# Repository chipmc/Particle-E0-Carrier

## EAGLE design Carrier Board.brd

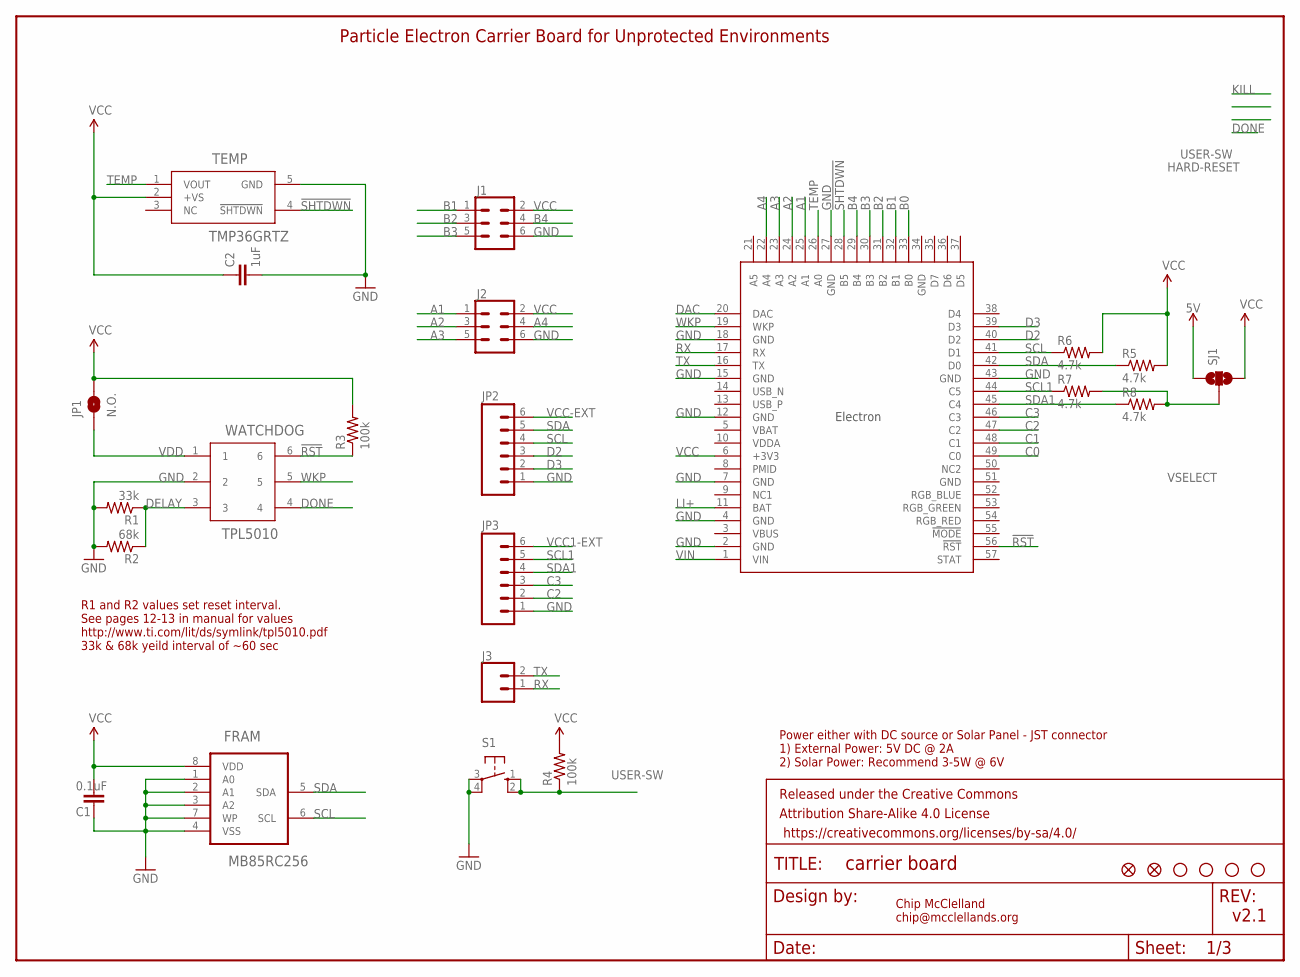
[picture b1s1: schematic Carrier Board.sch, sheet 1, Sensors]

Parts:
C1: 0.1uF; 0805
C2: 1uF; 0805
FD1, FD2: FIDUCIALUFIDUCIAL; FIDUCIAL-MICRO
FRAM: MB85RC256; SOIC127P600X175-8N
FRAME1: FRAME-LETTER; CREATIVE_COMMONS
J1, J2: CONN_03X22X3_SILK_MALE_PTH; 2X3
J3: CONN_02; 1X02
JP1: N.O.; SMT-JUMPER_2_NO_SILK
JP2, JP3: M06LOCK; 1X06_LOCK
JP4, JP5, JP6, JP7: STAND-OFF
R1: 33k; 0805
R2: 68k; 0805
R3, R4: 100k; 0805
R5, R6, R7, R8: 4.7k; 0805
S1: 10-XX; B3F-10XX
SJ1: SOLDERJUMPER_2WAYPASTE1&2; SJ_3_PASTE1&2
TEMP: TMP36GRTZ; RJ_5
U$1: E0-NOT-OFFICIAL
WATCHDOG: TPL5010; TSOT-23

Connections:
5V: SJ1.1; also elsewhere on the board
!RST: R3.1, U$1.56 (!RST), WATCHDOG.6
!SHTDWN: TEMP.4 (!SHTDWN), U$1.28 (B5)
A1: J2.1, U$1.25 (A1)
A2: J2.3, U$1.24 (A2)
A3: J2.5, U$1.23 (A3)
A4: J2.4, U$1.22 (A4)
B0: U$1.33 (B0)
B1: J1.1, U$1.32 (B1)
B2: J1.3, U$1.31 (B2)
B3: J1.5, U$1.30 (B3)
B4: J1.4, U$1.29 (B4)
C0: U$1.49 (C0)
C1: U$1.48 (C1)
C2: JP3.2, U$1.47 (C2); also elsewhere on the board
C3: JP3.3, U$1.46 (C3); also elsewhere on the board
D2: JP2.3, U$1.40 (D2); also elsewhere on the board
D3: JP2.2, U$1.39 (D3); also elsewhere on the board
DAC: U$1.20 (DAC)
DELAY: R1.1, R2.1, WATCHDOG.3
DONE: WATCHDOG.4
GND: C1.2, C2.2, FRAM.1 (A0), FRAM.2 (A1), FRAM.3 (A2), FRAM.4 (VSS), FRAM.7 (WP), J1.6, J2.6, JP2.1, JP3.1, R1.2, R2.2, S1.3, S1.4 (P1), TEMP.5 (GND), U$1.7 (GND), U$1.18 (GND), U$1.27 (GND), U$1.43 (GND), WATCHDOG.2; also elsewhere on the board
LI+: U$1.11 (BAT); also elsewhere on the board
RX: J3.1, U$1.17 (RX)
SCL: FRAM.6 (SCL), JP2.4, R6.1, U$1.41 (D1); also elsewhere on the board
SCL1: JP3.5, R7.1, U$1.44 (C5); also elsewhere on the board
SDA: FRAM.5 (SDA), JP2.5, R5.1, U$1.42 (D0); also elsewhere on the board
SDA1: JP3.4, R8.1, U$1.45 (C4); also elsewhere on the board
TEMP: TEMP.1 (VOUT), U$1.26 (A0)
TX: J3.2, U$1.16 (TX)
USER-SW: R4.1, S1.1 (S), S1.2 (S1)
VCC: C1.1, C2.1, FRAM.8 (VDD), J1.2, J2.2, JP1.2, R3.2, R4.2, R5.2, R6.2, SJ1.3, TEMP.2 (+VS), U$1.6 (+3V3); also elsewhere on the board
VCC1-EXT: JP3.6; also elsewhere on the board
VCC-EXT: JP2.6; also elsewhere on the board
VDD: JP1.1, WATCHDOG.1
VIN: U$1.1 (VIN); also elsewhere on the board
VSELECT: R7.2, R8.2, SJ1.2; also elsewhere on the board
WKP: U$1.19 (WKP), WATCHDOG.5

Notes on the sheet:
Chip McClelland chip@mcclellands.org
v2.1
Power either with DC source or Solar Panel - JST connector 1) External Power: 5V DC @ 2A 2) Solar Power: Recommend 3-5W @ 6V
Particle Electron Carrier Board for Unprotected Environments
R1 and R2 values set reset interval. See pages 12-13 in manual for values http://www.ti.com/lit/ds/symlink/tpl5010.pdf 33k & 68k yeild interval of ~60 sec

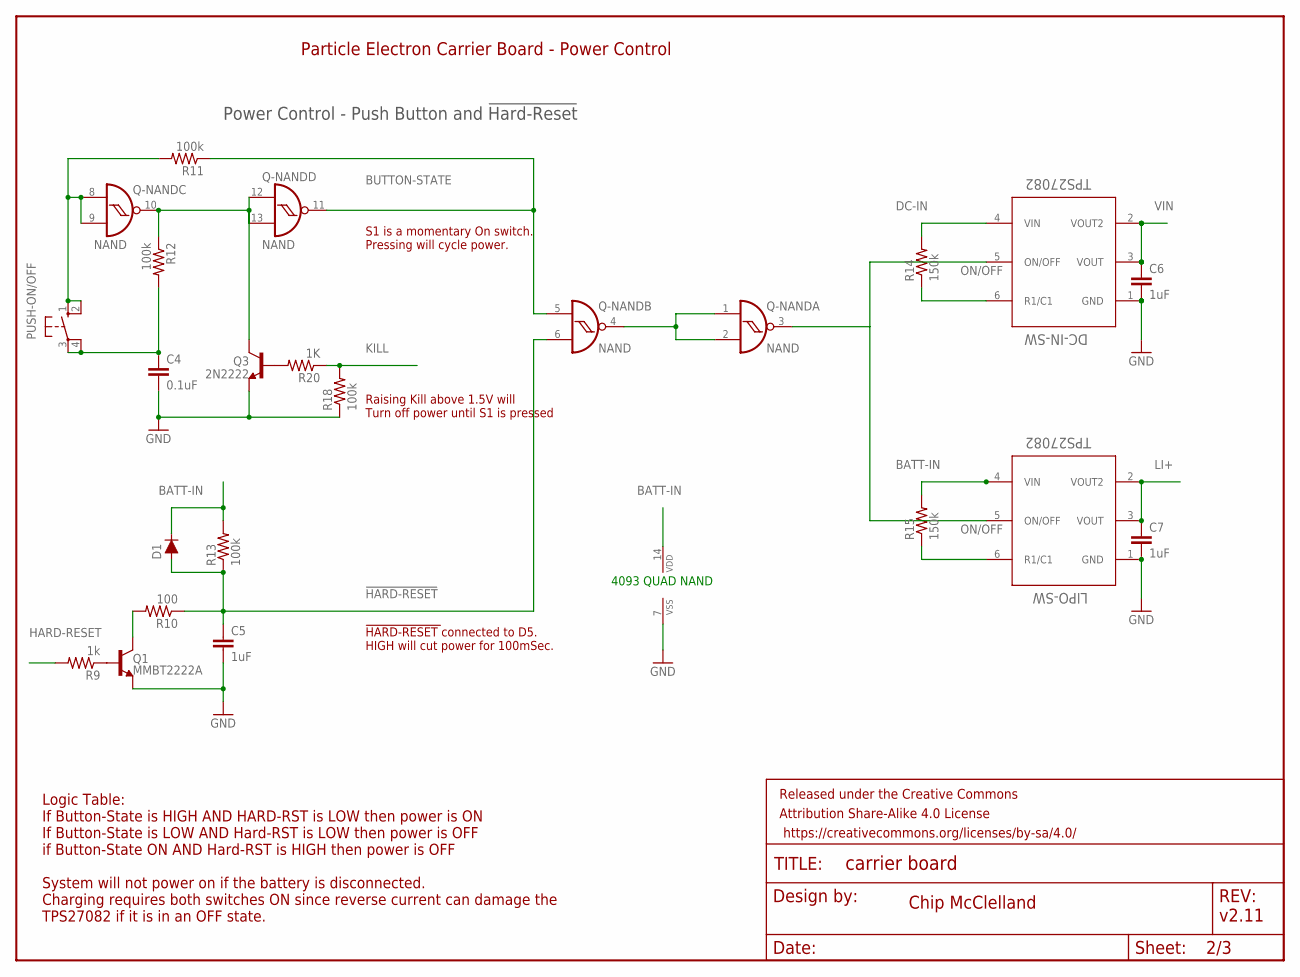
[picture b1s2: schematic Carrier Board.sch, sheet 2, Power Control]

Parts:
C4: 0.1uF; 0805
C5, C6, C7: 1uF; 0805
D1: DIODE-BAS16J; SOD-323
DC-IN-SW: TPS27082; TSOT-23
FRAME2: FRAME-LETTER; CREATIVE_COMMONS
LIPO-SW: TPS27082; TSOT-23
PUSH-ON/OFF: 40-XX-ROUND; B3F-40XX-ROUND
Q1: MMBT2222A; SOT23-3
Q3: 2N2222; SOT23-BEC
Q-NAND: NAND; MC14093B-TSSOP14
R9: 1k; 0805
R10: 100; 0805
R11, R12, R13, R18: 100k; 0805
R14, R15: 150k; 0805
R20: 1K; R0805

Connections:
!HARD-RESET: C5.1, D1.A, Q-NAND.6 (I1), R10.1, R13.1
BATT-IN: D1.C, LIPO-SW.4 (VIN), Q-NAND.14 (VDD), R13.2, R15.2; also elsewhere on the board
BUTTON-STATE: Q-NAND.5 (I0), Q-NAND.11 (O), R11.1
DC-IN: DC-IN-SW.4 (VIN), R14.2; also elsewhere on the board
GND: C4.2, C5.2, C6.2, C7.2, DC-IN-SW.1 (GND), LIPO-SW.1 (GND), Q1.2 (E), Q3.E, Q-NAND.7 (VSS), R18.1; also elsewhere on the board
HARD-RESET: R9.2
KILL: R18.2, R20.1
LI+: C7.1, LIPO-SW.2 (VOUT2), LIPO-SW.3 (VOUT); also elsewhere on the board
unnamed: Q-NAND.1 (I0), Q-NAND.2 (I1), Q-NAND.4 (O)
unnamed: Q3.B, R20.2
unnamed: Q3.C, Q-NAND.10 (O), Q-NAND.12 (I0), Q-NAND.13 (I1), R12.1
unnamed: DC-IN-SW.6 (R1/C1), R14.1
unnamed: Q1.1 (B), R9.1
unnamed: LIPO-SW.6 (R1/C1), R15.1
unnamed: Q1.3 (C), R10.2
unnamed: C4.1, PUSH-ON/OFF.3, PUSH-ON/OFF.4 (P1), R12.2
unnamed: PUSH-ON/OFF.1 (S), PUSH-ON/OFF.2 (S1), Q-NAND.8 (I0), Q-NAND.9 (I1), R11.2
ON/OFF: DC-IN-SW.5 (ON/OFF), LIPO-SW.5 (ON/OFF), Q-NAND.3 (O)
VIN: C6.1, DC-IN-SW.2 (VOUT2), DC-IN-SW.3 (VOUT); also elsewhere on the board

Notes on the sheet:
Particle Electron Carrier Board - Power Control
4093 QUAD NAND
Power Control - Push Button and !Hard-Reset
Chip McClelland
v2.11
Logic Table: If Button-State is HIGH AND HARD-RST is LOW then power is ON If Button-State is LOW AND Hard-RST is LOW then power is OFF if Button-State ON AND Hard-RST is HIGH then power is OFF System will not power on if the battery is disconnected. Charging requires both switches ON since reverse 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
!HARD-RESET !connected to D5. HIGH will cut power for 100mSec.
S1 is a momentary On switch. Pressing will cycle power.
Raising Kill above 1.5V will Turn off power until S1 is pressed

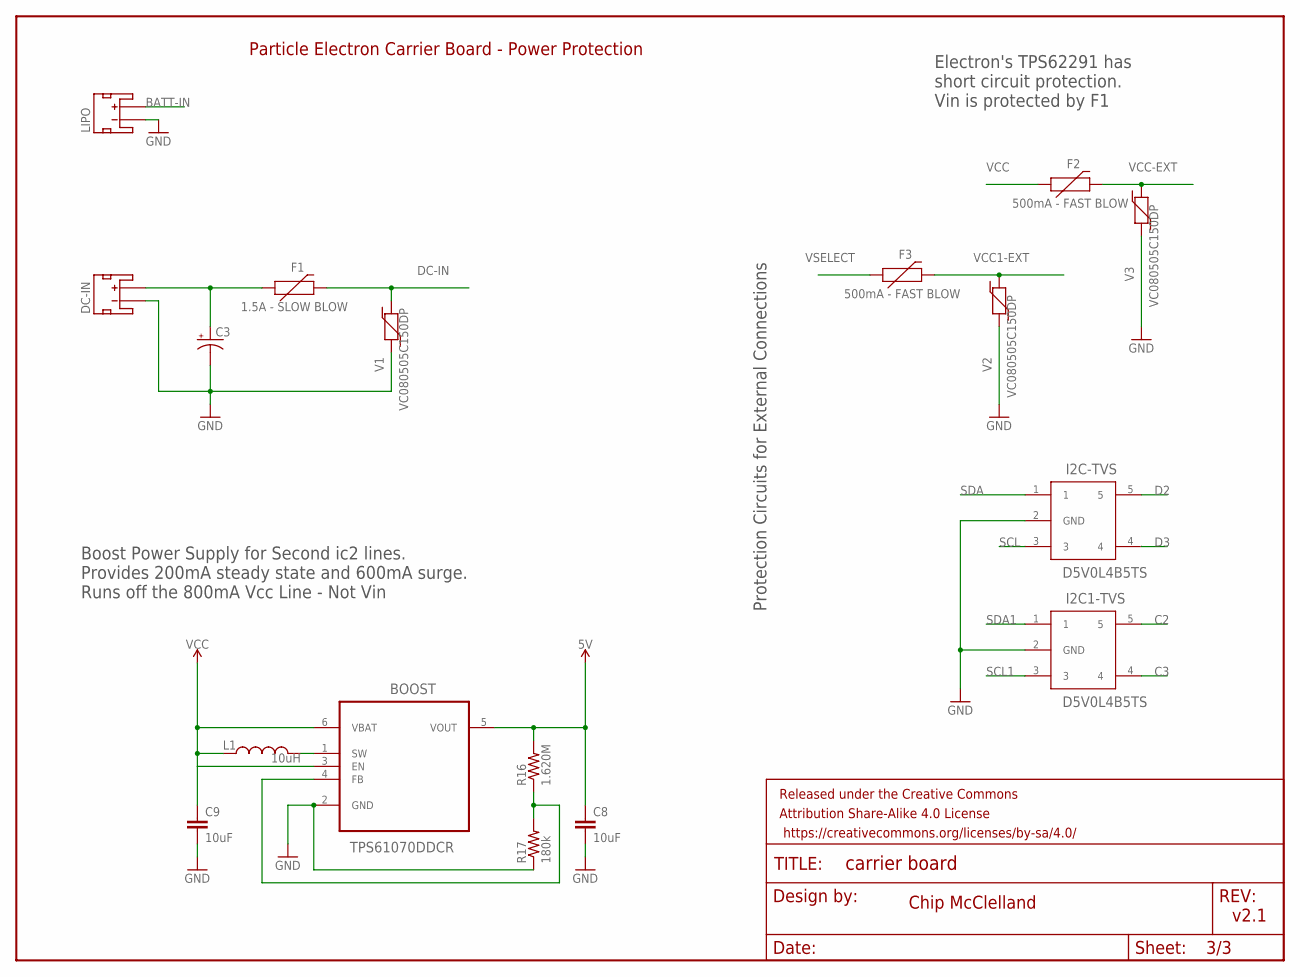
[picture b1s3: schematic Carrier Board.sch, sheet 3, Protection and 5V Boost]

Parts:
BOOST: TPS61070DDCR; SOT95P280X110-6N
C3: CAP_POLG; PANASONIC_G
C8, C9: 10uF; 0805
DC-IN: 5V @ 2A; JST-2-SMD
F1: 1.5A - SLOW BLOW; 1206
F2, F3: 500mA - FAST BLOW; 1206
FRAME3: FRAME-LETTER; CREATIVE_COMMONS
I2C1-TVS, I2C-TVS: D5V0L4B5TS; SOT-23-5
L1: 10uH; SDR0403
LIPO: JST_2MM_MALE; JST-2-SMD
R16: 1.620M; 0805
R17: 180k; 0805
V1, V2, V3: VC080505C150DP; 0805

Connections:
5V: BOOST.5 (VOUT), C8.1, R16.2; also elsewhere on the board
BATT-IN: LIPO.2 (+); also elsewhere on the board
C2: I2C1-TVS.5; also elsewhere on the board
C3: I2C1-TVS.4; also elsewhere on the board
D2: I2C-TVS.5; also elsewhere on the board
D3: I2C-TVS.4; also elsewhere on the board
DC-IN: C3.+, DC-IN.2 (+), F1.1, F1.2, V1.2; also elsewhere on the board
GND: BOOST.2 (GND), C3.-, C8.2, C9.2, DC-IN.1 (-), I2C1-TVS.2 (GND), I2C-TVS.2 (GND), LIPO.1 (-), R17.1, V1.1, V2.1, V3.1; also elsewhere on the board
unnamed: BOOST.4 (FB), R16.1, R17.2
SCL: I2C-TVS.3; also elsewhere on the board
SCL1: I2C1-TVS.3; also elsewhere on the board
SDA: I2C-TVS.1; also elsewhere on the board
SDA1: I2C1-TVS.1; also elsewhere on the board
SW: BOOST.1 (SW), L1.P$2 (2)
VCC: BOOST.3 (EN), BOOST.6 (VBAT), C9.1, F2.1, L1.P$1 (1); also elsewhere on the board
VCC1-EXT: F3.2, V2.2; also elsewhere on the board
VCC-EXT: F2.2, V3.2; also elsewhere on the board
VSELECT: F3.1; also elsewhere on the board

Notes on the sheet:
Protection Circuits for External Connections
Electron's TPS62291 has short circuit protection. Vin is protected by F1
Boost Power Supply for Second ic2 lines. Provides 200mA steady state and 600mA surge. Runs off the 800mA Vcc Line - Not Vin
Chip McClelland
v2.1
Particle Electron Carrier Board - Power Protection

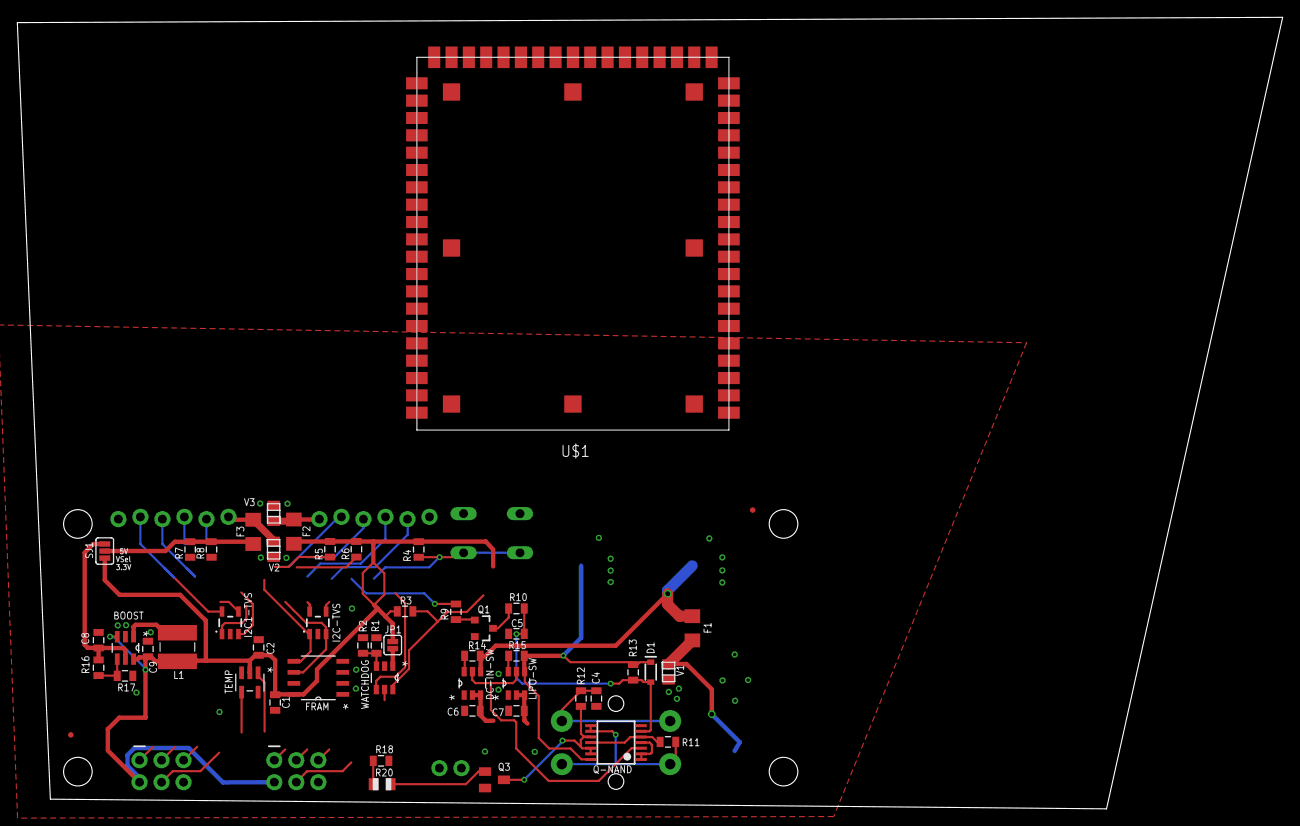
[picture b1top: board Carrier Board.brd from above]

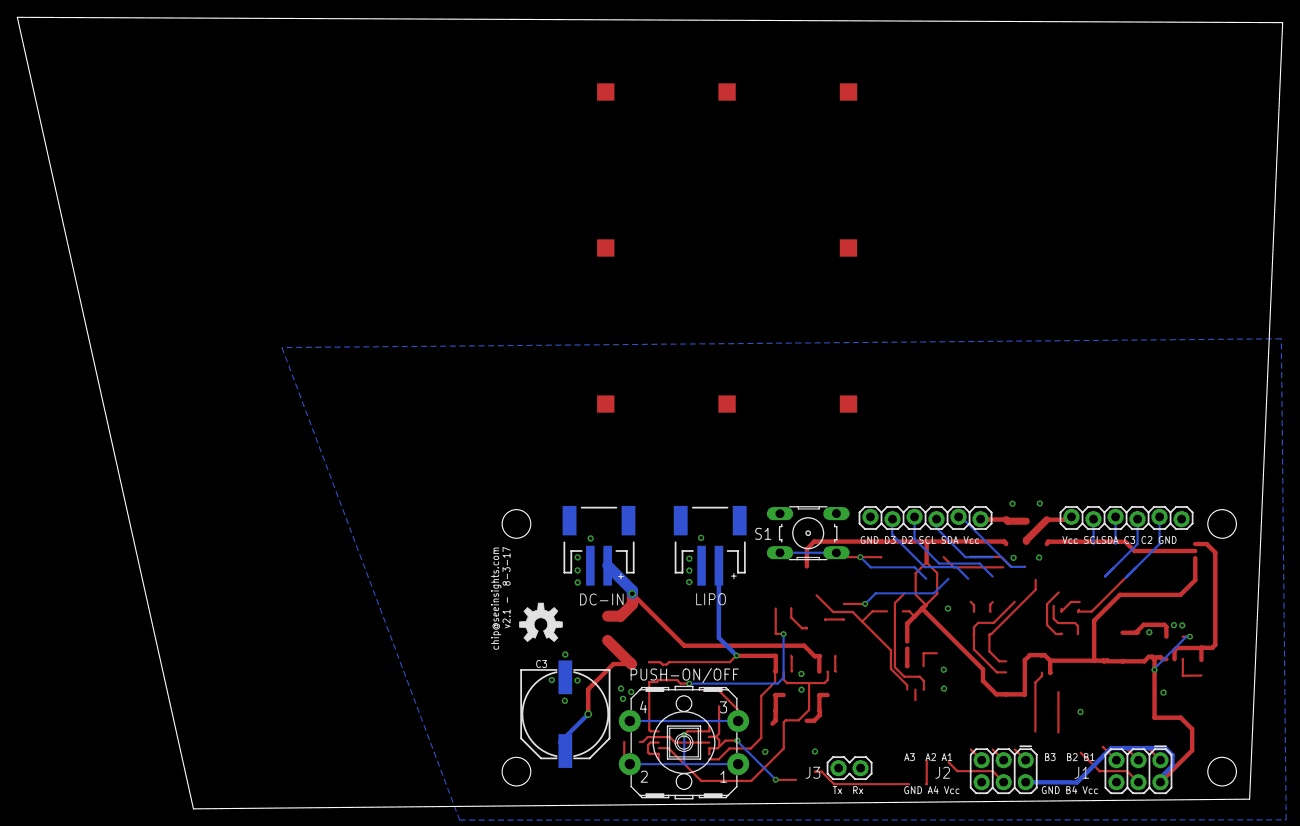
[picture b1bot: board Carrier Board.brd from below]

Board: 2 copper layers, 146.0 x 91.3 mm, 69 parts (11 on the bottom side), 50 nets.

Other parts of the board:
U$2: OSHW-LOGO-M

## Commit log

2017-10-21 Added EAGLE files and library
2018-12-19 Deleted

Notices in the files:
parts and their libraries:
SparkFun-Aesthetics: Licensing: Creative Commons ShareAlike 4.0 International - https://creativecommons.org/licenses/by-sa/4.0
SparkFun-Aesthetics: Released under the Creative Commons Attribution Share-Alike 4.0 License
SparkFun-Aesthetics: https://creativecommons.org/licenses/by-sa/4.0
